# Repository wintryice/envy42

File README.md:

This project is a passion project, I have no idea what I'm actually doing.

Plan to develop this board into an optimal daily driver.

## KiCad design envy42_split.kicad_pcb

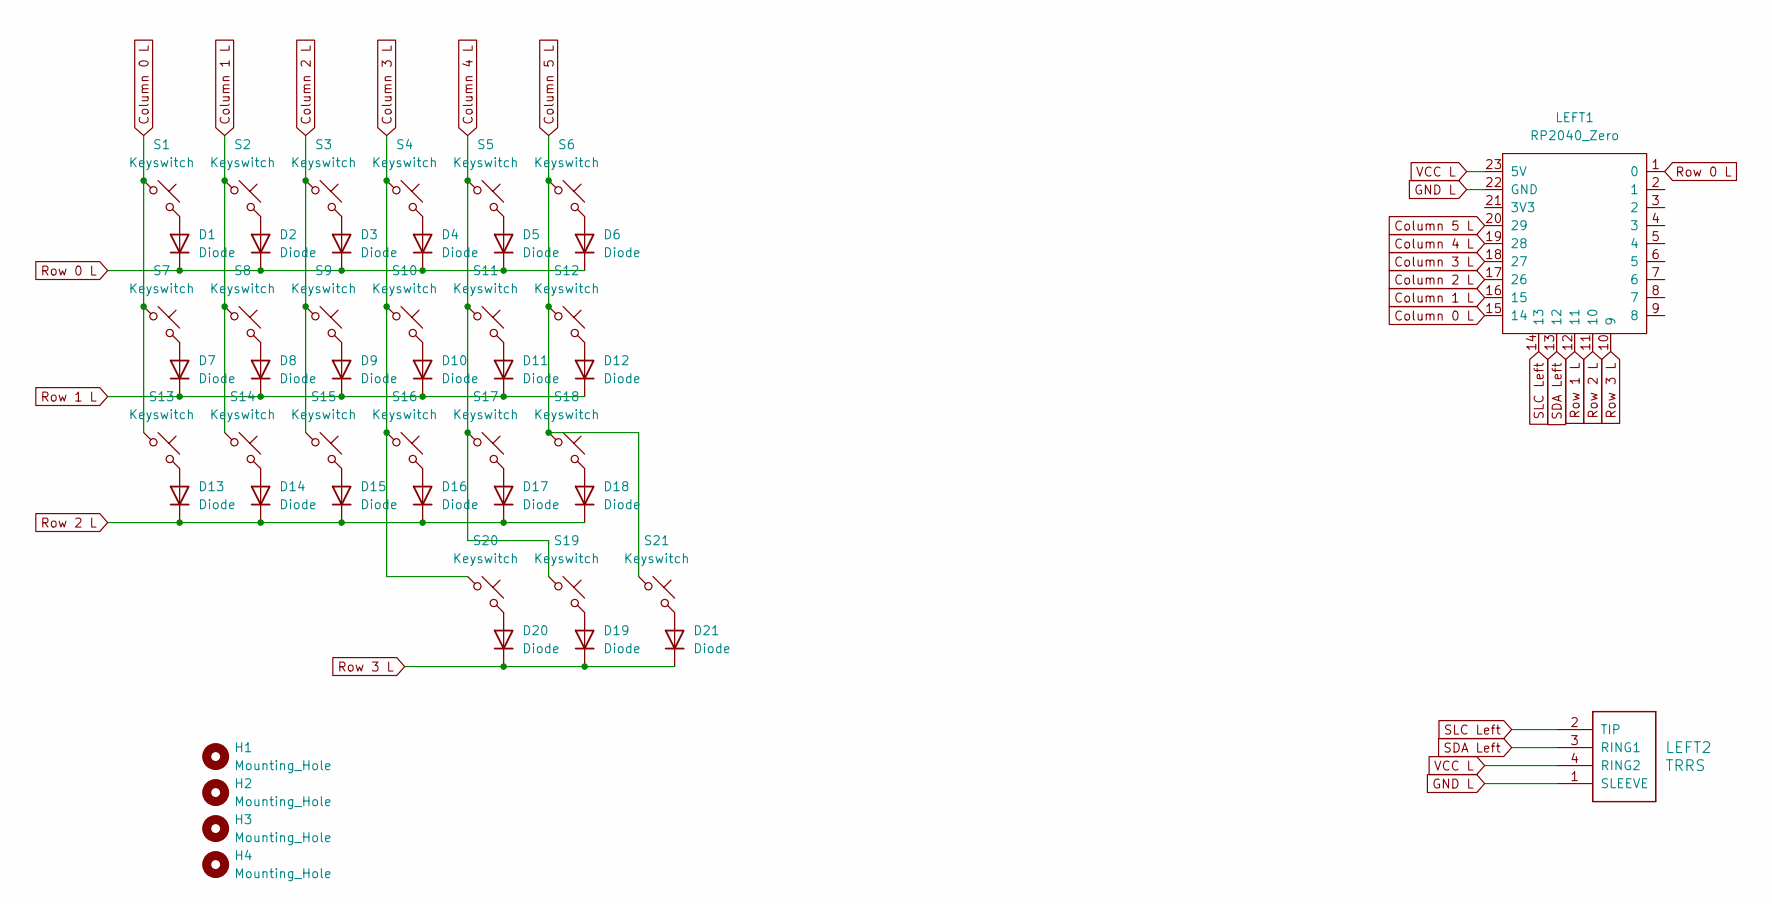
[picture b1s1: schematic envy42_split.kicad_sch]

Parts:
D1, D2, D3, D4, D5, D6, D7, D8, D9, D10, D11, D12, D13, D14, D15, D16, D17, D18, D19, D20, D21: Diode; Diode_DO-35
H1, H2, H3, H4: Mounting_Hole; MountingHole_2.2mm_M2_DIN965
LEFT1: RP2040_Zero
LEFT2: TRRS; TRRS_PJ-320A
S1, S2, S3, S4, S5, S6, S7, S8, S9, S10, S11, S12, S13, S14, S15, S16, S17, S18, S19, S20, S21: Keyswitch; MX_PCB_1.00u

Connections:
Column 0 L: LEFT1.15 (14), S1.1, S7.1, S13.1
Column 1 L: LEFT1.16 (15), S2.1, S8.1, S14.1
Column 2 L: LEFT1.17 (26), S3.1, S9.1, S15.1
Column 3 L: LEFT1.18 (27), S4.1, S10.1, S16.1, S20.1
Column 4 L: LEFT1.19 (28), S5.1, S11.1, S17.1, S19.1
Column 5 L: LEFT1.20 (29), S6.1, S12.1, S18.1, S21.1
GND L: LEFT1.22 (GND), LEFT2.1 (SLEEVE)
unnamed: D1.2 (A), S1.2
unnamed: D2.2 (A), S2.2
unnamed: D3.2 (A), S3.2
unnamed: D4.2 (A), S4.2
unnamed: D5.2 (A), S5.2
unnamed: D6.2 (A), S6.2
unnamed: D7.2 (A), S7.2
unnamed: D8.2 (A), S8.2
unnamed: D9.2 (A), S9.2
unnamed: D10.2 (A), S10.2
unnamed: D11.2 (A), S11.2
unnamed: D12.2 (A), S12.2
unnamed: D13.2 (A), S13.2
unnamed: D14.2 (A), S14.2
unnamed: D15.2 (A), S15.2
unnamed: D16.2 (A), S16.2
unnamed: D17.2 (A), S17.2
unnamed: D18.2 (A), S18.2
unnamed: D19.2 (A), S19.2
unnamed: D20.2 (A), S20.2
unnamed: D21.2 (A), S21.2
Row 0 L: D1.1 (K), D2.1 (K), D3.1 (K), D4.1 (K), D5.1 (K), D6.1 (K), LEFT1.1 (0)
Row 1 L: D7.1 (K), D8.1 (K), D9.1 (K), D10.1 (K), D11.1 (K), D12.1 (K), LEFT1.12 (11)
Row 2 L: D13.1 (K), D14.1 (K), D15.1 (K), D16.1 (K), D17.1 (K), D18.1 (K), LEFT1.11 (10)
Row 3 L: D19.1 (K), D20.1 (K), D21.1 (K), LEFT1.10 (9)
SDA Left: LEFT1.13 (12), LEFT2.3 (RING1)
SLC Left: LEFT1.14 (13), LEFT2.2 (TIP)
VCC L: LEFT1.23 (5V), LEFT2.4 (RING2)

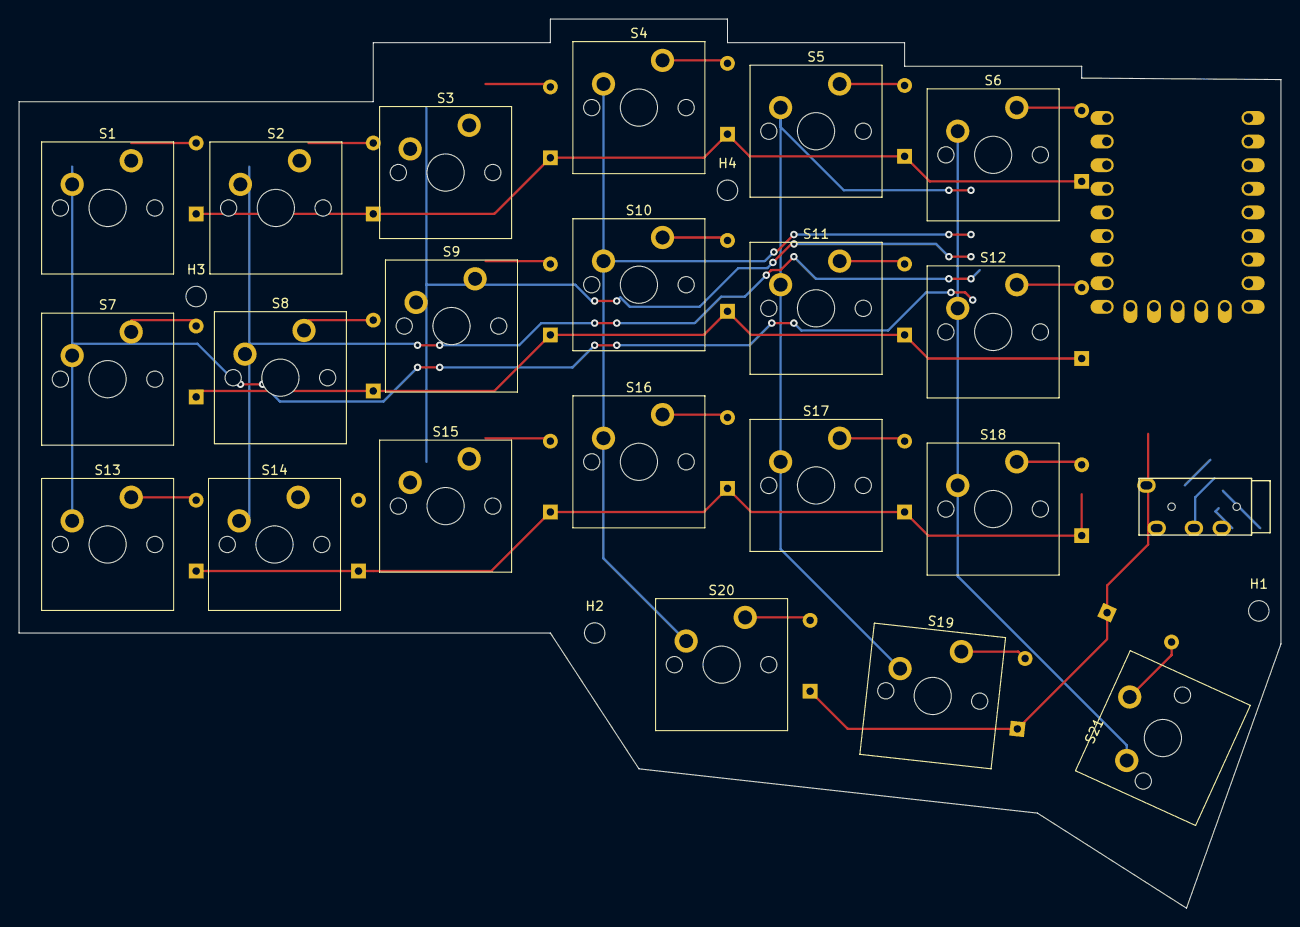
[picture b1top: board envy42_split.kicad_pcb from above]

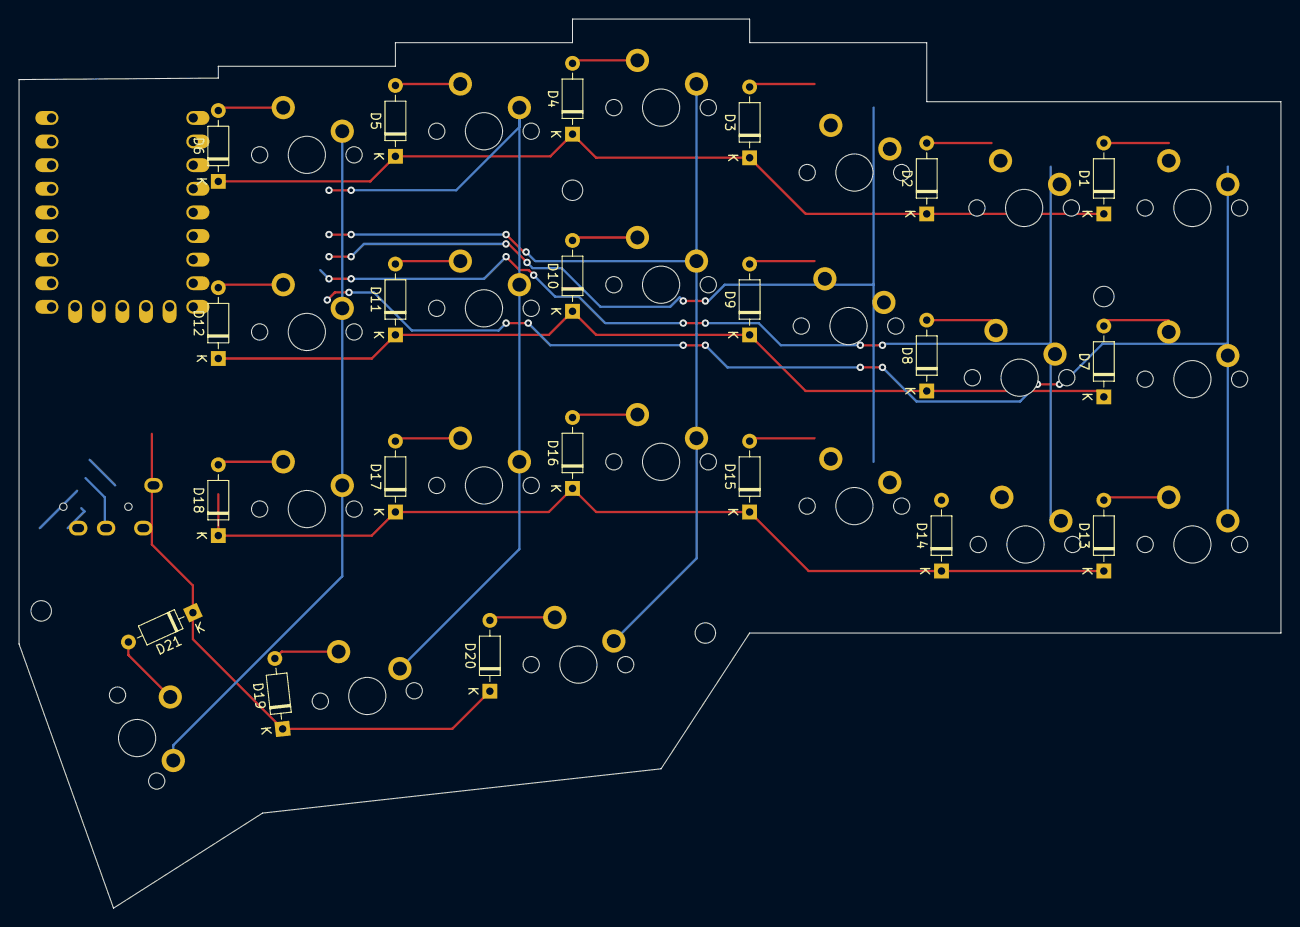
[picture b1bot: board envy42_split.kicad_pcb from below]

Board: 2 copper layers, 135.7 x 95.6 mm, 48 parts (21 on the bottom side), 35 nets.

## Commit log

2024-02-10 Create KiCad Files
2024-02-10 KiCad Files
    PCB layout and schematic
